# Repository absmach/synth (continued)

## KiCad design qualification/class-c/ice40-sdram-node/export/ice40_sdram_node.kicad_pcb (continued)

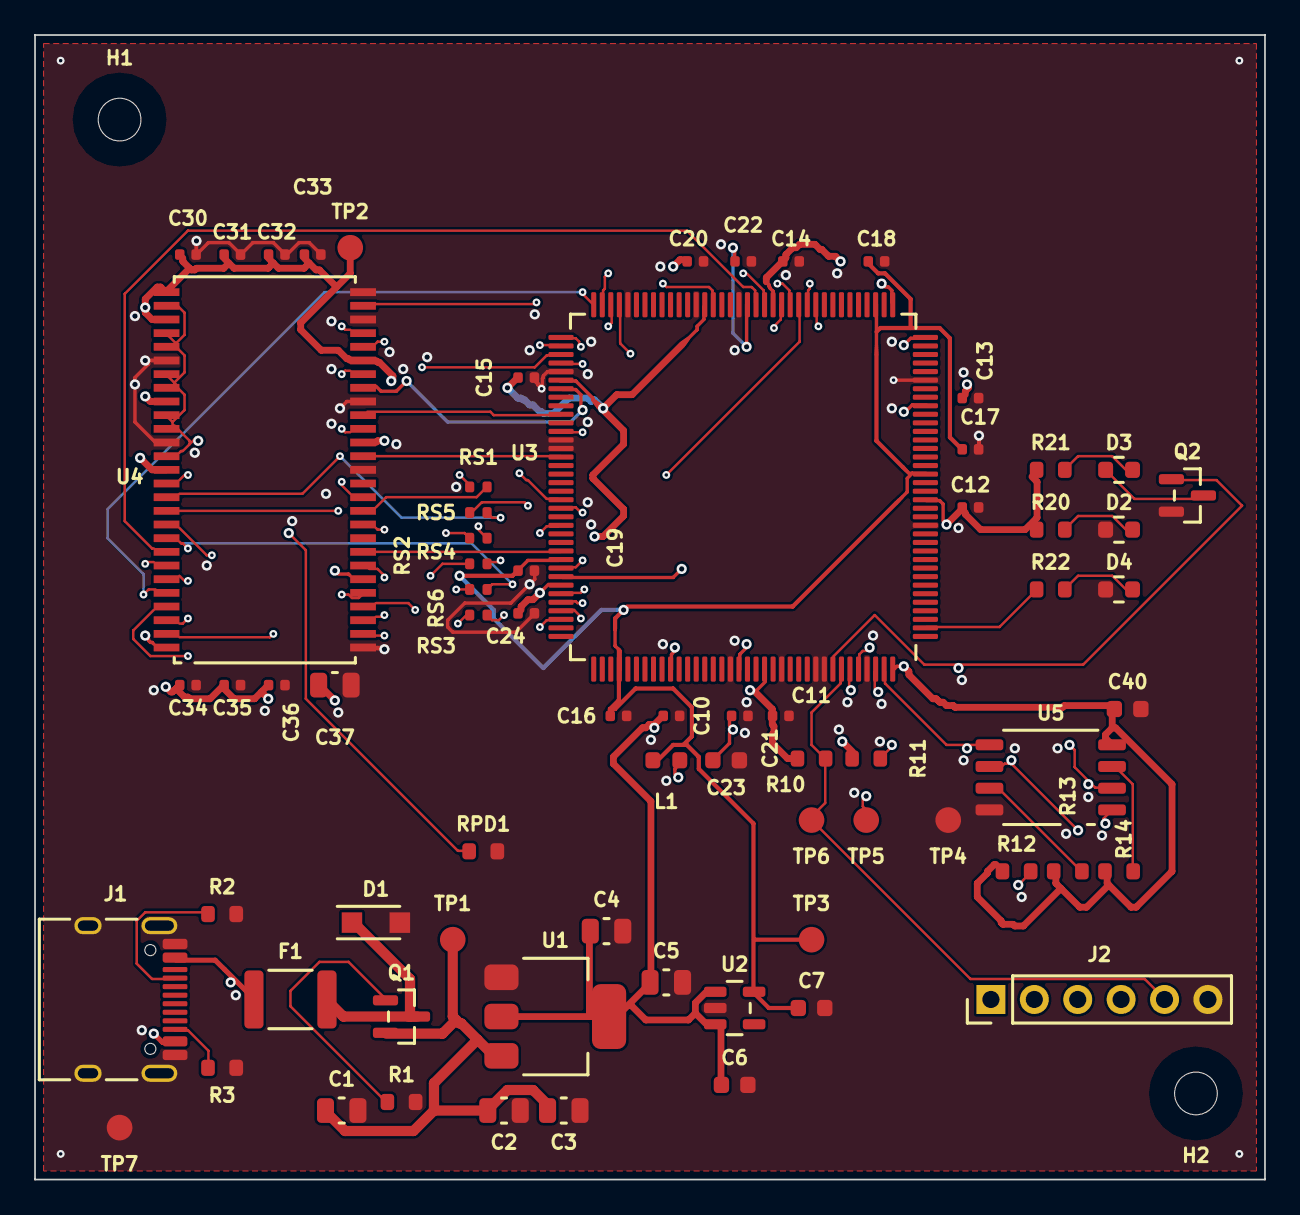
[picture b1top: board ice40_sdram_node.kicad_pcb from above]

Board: 6 copper layers, 72.0 x 67.0 mm, 73 parts (0 on the bottom side), 60 nets.

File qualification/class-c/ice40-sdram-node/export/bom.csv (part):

refdes,value,kind,description,kicad_symbol,kicad_footprint,lcsc_pn,mpn
C1,10uF,capacitor,"Generic 0805 MLCC, X7R/X5R, any value",Device:C,Capacitor_SMD:C_0805_2012Metric,,
C10,100nF,capacitor,"Generic 0402 MLCC, X7R/X5R, any value",Device:C,Capacitor_SMD:C_0402_1005Metric,,
C11,100nF,capacitor,"Generic 0402 MLCC, X7R/X5R, any value",Device:C,Capacitor_SMD:C_0402_1005Metric,,
C12,100nF,capacitor,"Generic 0402 MLCC, X7R/X5R, any value",Device:C,Capacitor_SMD:C_0402_1005Metric,,
C13,100nF,capacitor,"Generic 0402 MLCC, X7R/X5R, any value",Device:C,Capacitor_SMD:C_0402_1005Metric,,
C14,100nF,capacitor,"Generic 0402 MLCC, X7R/X5R, any value",Device:C,Capacitor_SMD:C_0402_1005Metric,,
C15,100nF,capacitor,"Generic 0402 MLCC, X7R/X5R, any value",Device:C,Capacitor_SMD:C_0402_1005Metric,,
C16,100nF,capacitor,"Generic 0402 MLCC, X7R/X5R, any value",Device:C,Capacitor_SMD:C_0402_1005Metric,,
C17,100nF,capacitor,"Generic 0402 MLCC, X7R/X5R, any value",Device:C,Capacitor_SMD:C_0402_1005Metric,,
C18,100nF,capacitor,"Generic 0402 MLCC, X7R/X5R, any value",Device:C,Capacitor_SMD:C_0402_1005Metric,,
C19,100nF,capacitor,"Generic 0402 MLCC, X7R/X5R, any value",Device:C,Capacitor_SMD:C_0402_1005Metric,,
C2,10uF,capacitor,"Generic 0805 MLCC, X7R/X5R, any value",Device:C,Capacitor_SMD:C_0805_2012Metric,,
C20,100nF,capacitor,"Generic 0402 MLCC, X7R/X5R, any value",Device:C,Capacitor_SMD:C_0402_1005Metric,,
C21,100nF,capacitor,"Generic 0402 MLCC, X7R/X5R, any value",Device:C,Capacitor_SMD:C_0402_1005Metric,,
C22,100nF,capacitor,"Generic 0402 MLCC, X7R/X5R, any value",Device:C,Capacitor_SMD:C_0402_1005Metric,,
C23,1uF,capacitor,"Generic 0603 MLCC, X7R/X5R, any value",Device:C,Capacitor_SMD:C_0603_1608Metric,,
C24,100nF,capacitor,"Generic 0402 MLCC, X7R/X5R, any value",Device:C,Capacitor_SMD:C_0402_1005Metric,,
C3,10uF,capacitor,"Generic 0805 MLCC, X7R/X5R, any value",Device:C,Capacitor_SMD:C_0805_2012Metric,,
C30,100nF,capacitor,"Generic 0402 MLCC, X7R/X5R, any value",Device:C,Capacitor_SMD:C_0402_1005Metric,,
C31,100nF,capacitor,"Generic 0402 MLCC, X7R/X5R, any value",Device:C,Capacitor_SMD:C_0402_1005Metric,,
C32,100nF,capacitor,"Generic 0402 MLCC, X7R/X5R, any value",Device:C,Capacitor_SMD:C_0402_1005Metric,,
C33,100nF,capacitor,"Generic 0402 MLCC, X7R/X5R, any value",Device:C,Capacitor_SMD:C_0402_1005Metric,,
C34,100nF,capacitor,"Generic 0402 MLCC, X7R/X5R, any value",Device:C,Capacitor_SMD:C_0402_1005Metric,,
C35,100nF,capacitor,"Generic 0402 MLCC, X7R/X5R, any value",Device:C,Capacitor_SMD:C_0402_1005Metric,,
C36,100nF,capacitor,"Generic 0402 MLCC, X7R/X5R, any value",Device:C,Capacitor_SMD:C_0402_1005Metric,,
C37,10uF,capacitor,"Generic 0805 MLCC, X7R/X5R, any value",Device:C,Capacitor_SMD:C_0805_2012Metric,,
C4,10uF,capacitor,"Generic 0805 MLCC, X7R/X5R, any value",Device:C,Capacitor_SMD:C_0805_2012Metric,,
C40,100nF,capacitor,"Generic 0603 MLCC, X7R/X5R, any value",Device:C,Capacitor_SMD:C_0603_1608Metric,,
C5,10uF,capacitor,"Generic 0805 MLCC, X7R/X5R, any value",Device:C,Capacitor_SMD:C_0805_2012Metric,,
C6,1uF,capacitor,"Generic 0603 MLCC, X7R/X5R, any value",Device:C,Capacitor_SMD:C_0603_1608Metric,,
C7,1uF,capacitor,"Generic 0603 MLCC, X7R/X5R, any value",Device:C,Capacitor_SMD:C_0603_1608Metric,,
D1,PTVS6V0S1UR,diode,"Nexperia PTVS6V0S1UR 400 W unidirectional TVS, 6.0 V standoff, SOD123W, for VBUS and CC",Device:D_Zener,Diode_SMD:Nexperia_CFP3_SOD-123W,,PTVS6V0S1UR
D2,0603-RED,diode,"Red LED, 0603 package, ~2.0V Vf",Device:LED,LED_SMD:LED_0603_1608Metric,C2286,0603-RED
D3,0603-GREEN,diode,"Green LED, 0603 package, ~2.2V Vf",Device:LED,LED_SMD:LED_0603_1608Metric,C72043,0603-GREEN
D4,0603-GREEN,diode,"Green LED, 0603 package, ~2.2V Vf",Device:LED,LED_SMD:LED_0603_1608Metric,C72043,0603-GREEN
F1,MF-MSMF110/16-2,fuse,"Bourns MF-MSMF110/16-2 resettable fuse, 1.1 A hold, 16 V, 1812",Device:Polyfuse,Fuse:Fuse_1812_4532Metric,C210834,MF-MSMF110/16-2
H1,(no value),mounting_hole,M2.5 non-plated mounting hole (NPTH) for a board corner,Mechanical:MountingHole,MountingHole:MountingHole_2.5mm,,
H2,(no value),mounting_hole,M2.5 non-plated mounting hole (NPTH) for a board corner,Mechanical:MountingHole,MountingHole:MountingHole_2.5mm,,
J1,TYPE-C-31-M-12,connector,"USB-C receptacle, 24-pin SMD. Modelled here with primary and mirrored power/ground/data pins for full pad coverage.",Connector:USB_C_Receptacle,Connector_USB:USB_C_Receptacle_HRO_TYPE-C-31-M-12,C165948,TYPE-C-31-M-12
J2,(no value),connector,"1x6 through-hole pin header, 2.54 mm pitch, vertical, hand-fitted iCE40 SPI programming port (SPI_SS_B, SPI_SCK, SPI_SDI, SPI_SDO, CRESET_B, GND). No current rating asserted; no MPN or LCSC number asserted.",Connector_Generic:Conn_01x06,Connector_PinHeader_2.54mm:PinHeader_1x06_P2.54mm_Vertical,,
L1,(no value),inductor,"0603 ferrite bead, 600Ω @ 100MHz — EMI suppression",Device:FerriteBead,Inductor_SMD:L_0603_1608Metric,,
Q1,SI2301CDS-T1-GE3,transistor,"Vishay Si2301 P-channel power MOSFET, SOT-23",Transistor_FET:Si2301CDS,Package_TO_SOT_SMD:SOT-23,C10487,SI2301CDS-T1-GE3
Q2,AO3400A,transistor,"Alpha&Omega AO3400A 30 V N-channel MOSFET, SOT-23: ID 5.7 A at 25 C, Rds(on) under 26.5 mOhm at Vgs 10 V, 32 mOhm at 4.5 V and 48 mOhm at 2.5 V, Vgs +/-12 V",Transistor_FET:AO3400A,Package_TO_SOT_SMD:SOT-23,,AO3400A
R1,10k,resistor,"Generic 0603 thick-film resistor, any value",Device:R_US,Resistor_SMD:R_0603_1608Metric,,
R10,10k,resistor,"Generic 0603 thick-film resistor, any value",Device:R_US,Resistor_SMD:R_0603_1608Metric,,
R11,10k,resistor,"Generic 0603 thick-film resistor, any value",Device:R_US,Resistor_SMD:R_0603_1608Metric,,
R12,10k,resistor,"Generic 0603 thick-film resistor, any value",Device:R_US,Resistor_SMD:R_0603_1608Metric,,
R13,10k,resistor,"Generic 0603 thick-film resistor, any value",Device:R_US,Resistor_SMD:R_0603_1608Metric,,
R14,10k,resistor,"Generic 0603 thick-film resistor, any value",Device:R_US,Resistor_SMD:R_0603_1608Metric,,
R2,5.1k,resistor,"Generic 0603 thick-film resistor, any value",Device:R_US,Resistor_SMD:R_0603_1608Metric,,
R20,1k,resistor,"Generic 0603 thick-film resistor, any value",Device:R_US,Resistor_SMD:R_0603_1608Metric,,
R21,1k,resistor,"Generic 0603 thick-film resistor, any value",Device:R_US,Resistor_SMD:R_0603_1608Metric,,
R22,1k,resistor,"Generic 0603 thick-film resistor, any value",Device:R_US,Resistor_SMD:R_0603_1608Metric,,
R3,5.1k,resistor,"Generic 0603 thick-film resistor, any value",Device:R_US,Resistor_SMD:R_0603_1608Metric,,
RPD1,10k,resistor,"Generic 0603 thick-film resistor, any value",Device:R_US,Resistor_SMD:R_0603_1608Metric,,
RS1,22,resistor,"Generic 0402 thick-film resistor, any value",Device:R_US,Resistor_SMD:R_0402_1005Metric,,
RS2,22,resistor,"Generic 0402 thick-film resistor, any value",Device:R_US,Resistor_SMD:R_0402_1005Metric,,
RS3,22,resistor,"Generic 0402 thick-film resistor, any value",Device:R_US,Resistor_SMD:R_0402_1005Metric,,
RS4,22,resistor,"Generic 0402 thick-film resistor, any value",Device:R_US,Resistor_SMD:R_0402_1005Metric,,
RS5,22,resistor,"Generic 0402 thick-film resistor, any value",Device:R_US,Resistor_SMD:R_0402_1005Metric,,
RS6,22,resistor,"Generic 0402 thick-film resistor, any value",Device:R_US,Resistor_SMD:R_0402_1005Metric,,
TP1,(no value),testpoint,"SMD test point pad, 1.5 mm — probe point for a net",Connector:TestPoint,TestPoint:TestPoint_Pad_D1.5mm,,
TP2,(no value),testpoint,"SMD test point pad, 1.5 mm — probe point for a net",Connector:TestPoint,TestPoint:TestPoint_Pad_D1.5mm,,
TP3,(no value),testpoint,"SMD test point pad, 1.5 mm — probe point for a net",Connector:TestPoint,TestPoint:TestPoint_Pad_D1.5mm,,
TP4,(no value),testpoint,"SMD test point pad, 1.5 mm — probe point for a net",Connector:TestPoint,TestPoint:TestPoint_Pad_D1.5mm,,
TP5,(no value),testpoint,"SMD test point pad, 1.5 mm — probe point for a net",Connector:TestPoint,TestPoint:TestPoint_Pad_D1.5mm,,
TP6,(no value),testpoint,"SMD test point pad, 1.5 mm — probe point for a net",Connector:TestPoint,TestPoint:TestPoint_Pad_D1.5mm,,
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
